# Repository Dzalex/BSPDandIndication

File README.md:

# BSPDandIndication
Used to implement BSPD and safety circuit status for Alumni car of Road Arrow Belgrade.

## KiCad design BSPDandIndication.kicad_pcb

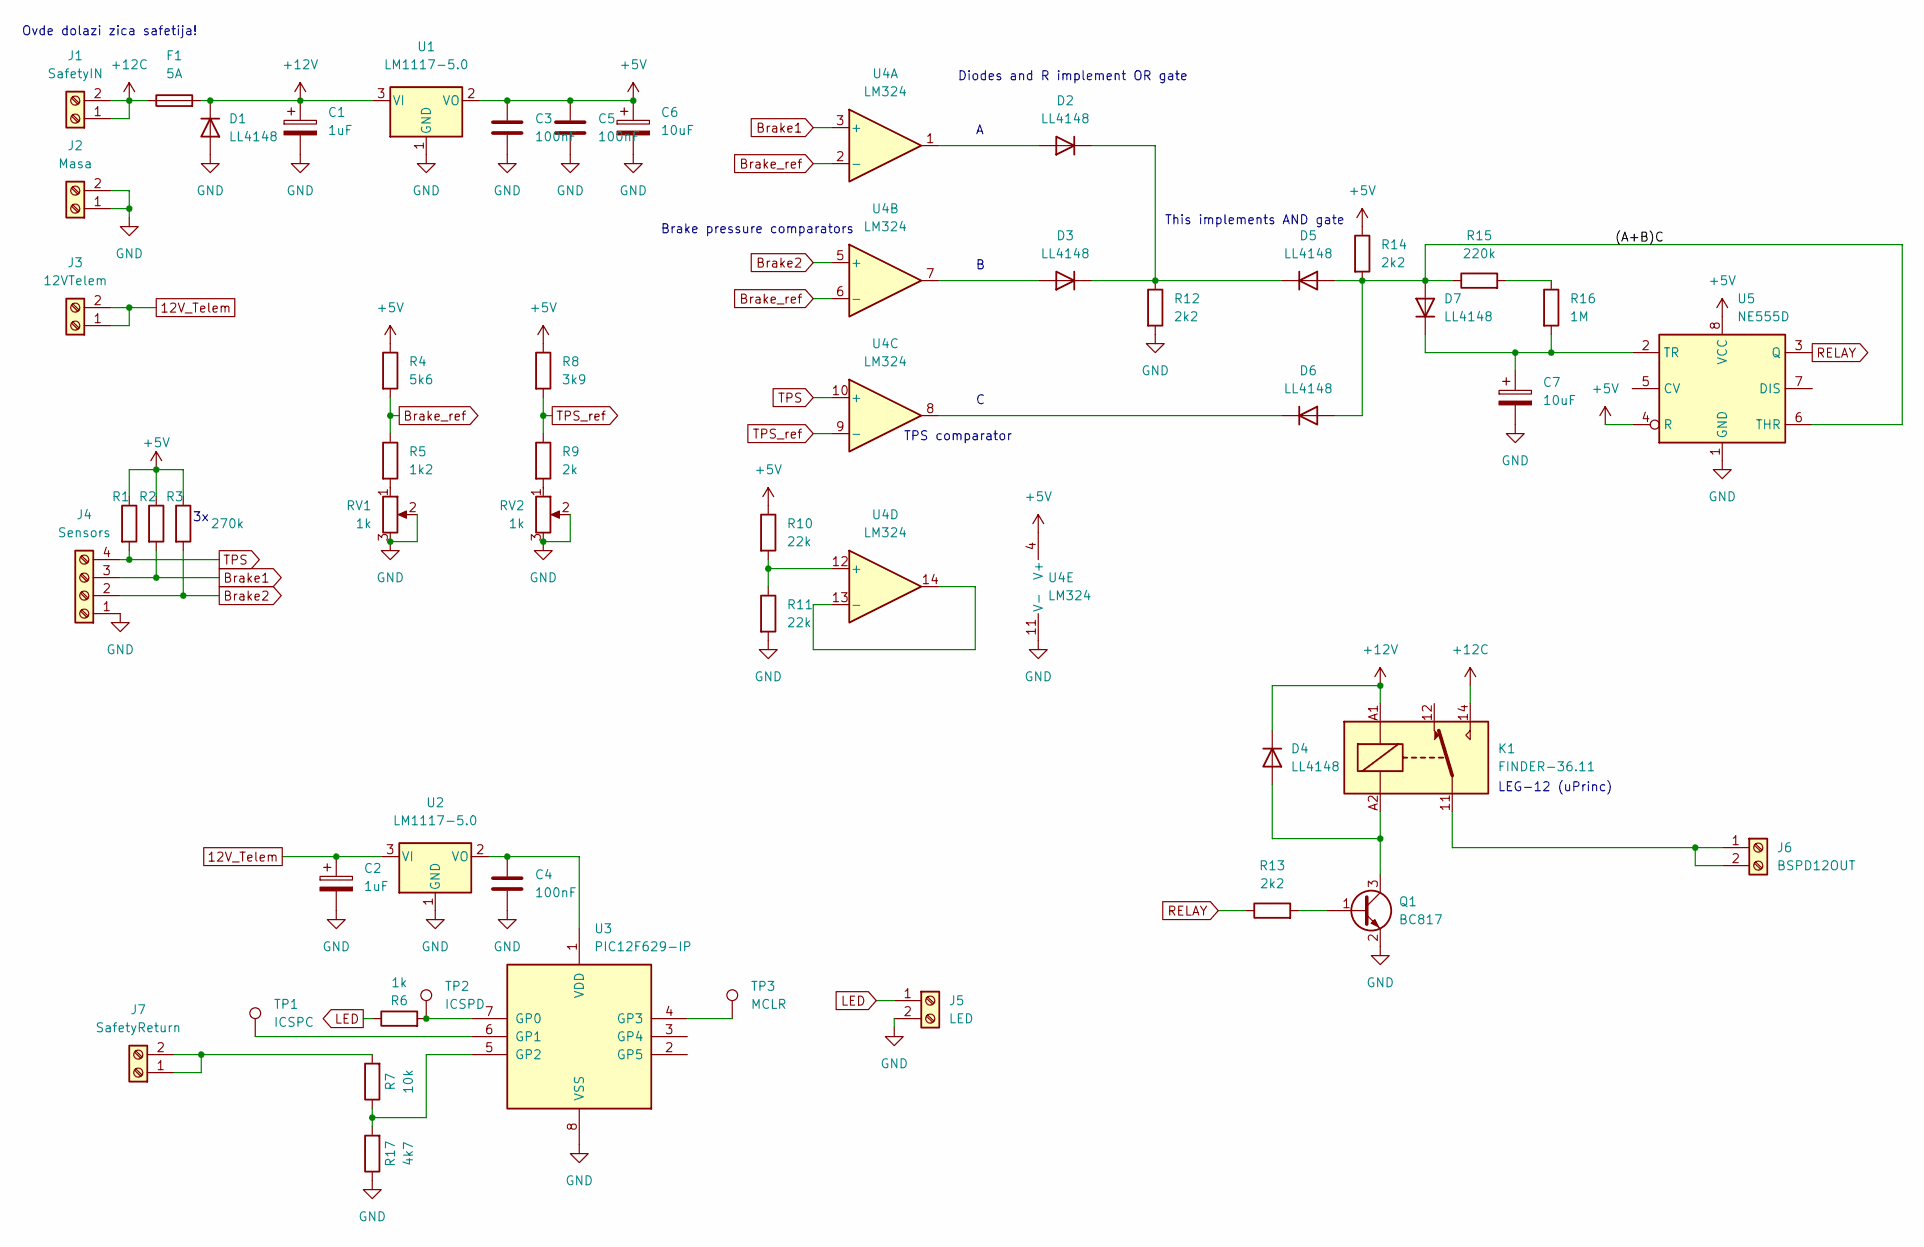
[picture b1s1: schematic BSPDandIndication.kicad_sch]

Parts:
C1, C2: 1uF; CP_EIA-3216-18_Kemet-A_Pad1.58x1.35mm_HandSolder
C3, C4, C5: 100nF; C_1206_3216Metric_Pad1.33x1.80mm_HandSolder
C6, C7: 10uF; CP_EIA-3216-18_Kemet-A_Pad1.58x1.35mm_HandSolder
D1, D2, D3, D4, D5, D6, D7: LL4148; D_MiniMELF
F1: 5A; Fuseholder_Cylinder-5x20mm_Schurter_0031_8201_Horizontal_Op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
J1: SafetyIN; AK300_1x02_P5.00mm_45-Degree
J2: Masa; AK300_1x02_P5.00mm_45-Degree
J3: 12VTelem; AK300_1x02_P5.00mm_45-Degree
J4: Sensors; AK3001_1x04_P5.00mm_45-Degree
J5: LED; AK300_1x02_P5.00mm_45-Degree
J6: BSPD12OUT; AK300_1x02_P5.00mm_45-Degree
J7: SafetyReturn; AK300_1x02_P5.00mm_45-Degree
K1: FINDER-36.11; Relay_SPDT_Finder_36.11
Q1: BC817; SOT-23
R1, R2, R3: 270k; R_1206_3216Metric_Pad1.30x1.75mm_HandSolder
R4: 5k6; R_1206_3216Metric_Pad1.30x1.75mm_HandSolder
R5: 1k2; R_1206_3216Metric_Pad1.30x1.75mm_HandSolder
R6: 1k; R_1206_3216Metric_Pad1.30x1.75mm_HandSolder
R7: 10k; R_1206_3216Metric_Pad1.30x1.75mm_HandSolder
R8: 3k9; R_1206_3216Metric_Pad1.30x1.75mm_HandSolder
R9: 2k; R_1206_3216Metric_Pad1.30x1.75mm_HandSolder
R10, R11: 22k; R_1206_3216Metric_Pad1.30x1.75mm_HandSolder
R12, R13, R14: 2k2; R_1206_3216Metric_Pad1.30x1.75mm_HandSolder
R15: 220k; R_1206_3216Metric_Pad1.30x1.75mm_HandSolder
R16: 1M; R_1206_3216Metric_Pad1.30x1.75mm_HandSolder
R17: 4k7; R_1206_3216Metric_Pad1.30x1.75mm_HandSolder
RV1, RV2: 1k; Potentiometer_Vishay_TS53YL_Vertical
TP1: ICSPC; TestPoint_Pad_2.5x2.5mm
TP2: ICSPD; TestPoint_Pad_2.5x2.5mm
TP3: MCLR; TestPoint_Pad_2.5x2.5mm
U1, U2: LM1117-5.0; SOT-223
U3: PIC12F629-IP; DIP-8_W7.62mm
U4: LM324; SO-14_3.9x8.65mm_P1.27mm
U5: NE555D; SOIC-8_3.9x4.9mm_P1.27mm

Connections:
12V_Telem: C2.1, J3.1, J3.2, U2.3 (VI)
+5V: C3.1, C5.1, C6.1, R1.1, R2.1, R3.1, R4.1, R8.1, R10.1, R14.1, U1.2 (VO), U4.4 (V+), U5.4 (R), U5.8 (VCC)
+12C: F1.1, J1.1, J1.2, K1.14
+12V: C1.1, D1.1 (K), D4.1 (K), F1.2, K1.A1, U1.3 (VI)
/(A+B)C: D5.2 (A), D6.2 (A), D7.2 (A), R14.2, R15.1, U5.6 (THR)
Brake1: J4.3, R2.2, U4.3 (+)
Brake2: J4.2, R3.2, U4.5 (+)
Brake_ref: R4.2, R5.1, U4.2 (-), U4.6 (-)
GND: C1.2, C2.2, C3.2, C4.2, C5.2, C6.2, C7.2, D1.2 (A), J2.1, J2.2, J4.1, J5.2, Q1.2 (E), R11.2, R12.2, R17.1, RV1.2, RV1.3, RV2.2, RV2.3, U1.1 (GND), U2.1 (GND), U3.8 (VSS), U4.11 (V-), U5.1 (GND)
LED: J5.1, R6.1
unnamed: C4.1, U2.2 (VO), U3.1 (VDD)
unnamed: C7.1, D7.1 (K), R16.2, U5.2 (TR)
unnamed: D2.1 (K), D3.1 (K), D5.1 (K), R12.1
unnamed: D2.2 (A), U4.1
unnamed: D3.2 (A), U4.7
unnamed: D4.2 (A), K1.A2, Q1.3 (C)
unnamed: D6.1 (K), U4.8
unnamed: J7.1, J7.2, R7.2
unnamed: J6.1, J6.2, K1.11
unnamed: Q1.1 (B), R13.2
unnamed: R5.2, RV1.1
unnamed: R6.2, TP2.1, U3.7 (GP0)
unnamed: R9.2, RV2.1
unnamed: R10.2, R11.1, U4.12 (+)
unnamed: R15.2, R16.1
unnamed: R7.1, R17.2, U3.5 (GP2)
unnamed: TP1.1, U3.6 (GP1)
unnamed: TP3.1, U3.4 (GP3)
unnamed: U4.13 (-), U4.14
RELAY: R13.1, U5.3 (Q)
TPS: J4.4, R1.2, U4.10 (+)
TPS_ref: R8.2, R9.1, U4.9 (-)

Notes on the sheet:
TPS comparator
Diodes and R implement OR gate
Ovde dolazi zica safetija!
This implements AND gate
LEG-12 (uPrinc)
Brake pressure comparators

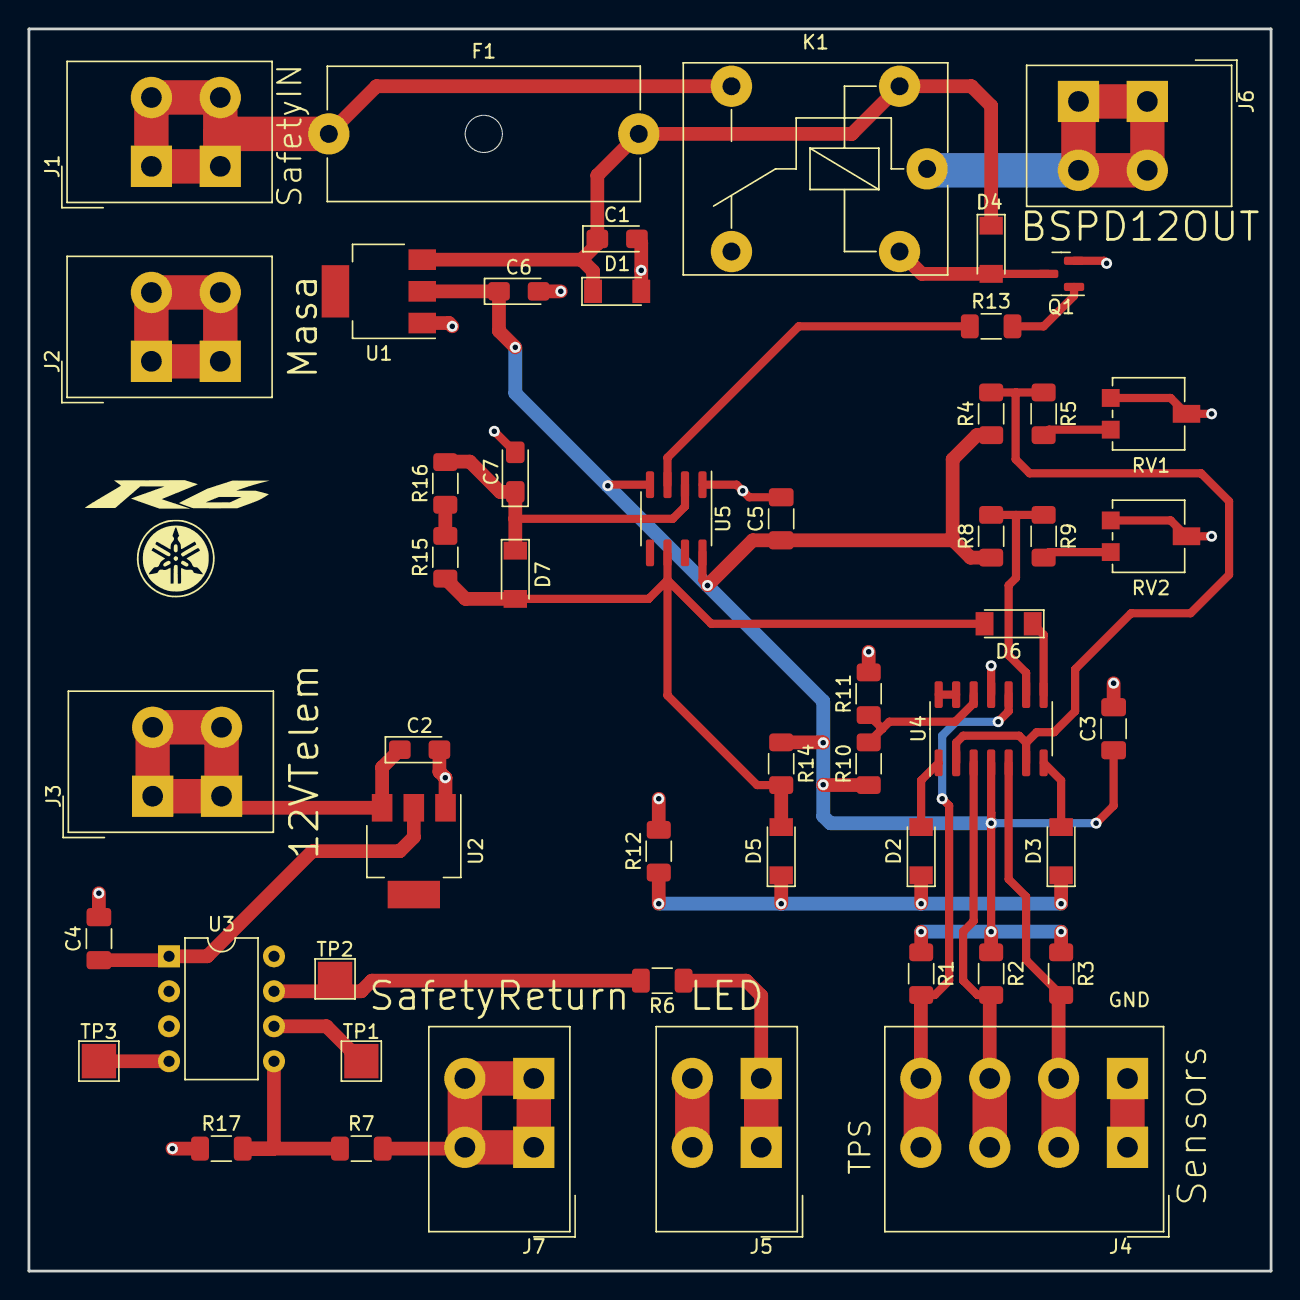
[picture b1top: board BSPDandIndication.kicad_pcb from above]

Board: 2 copper layers, 90.2 x 90.2 mm, 52 parts (0 on the bottom side), 32 nets.

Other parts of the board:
Log1: LOGO; r6 logo

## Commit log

2022-06-12 Add .gitignore
2022-06-12 Add first version of schematic and add components to PCB
2022-06-12 Update J5 value
2022-06-12 Return safety pin (to recognize when safety fail)
2022-06-29 Only one fuse needed
2022-06-29 Arrange components regarding PIC12f
2022-06-30 First version of route
2022-07-01 Fix DRC issues
2022-07-08 Add logo, r6, to project
2022-07-08 Add logo to PCB and final edit
2022-07-08 Create gerbers
2022-08-15 Commit latest changes
2025-06-23 Update project to KiCad 9
